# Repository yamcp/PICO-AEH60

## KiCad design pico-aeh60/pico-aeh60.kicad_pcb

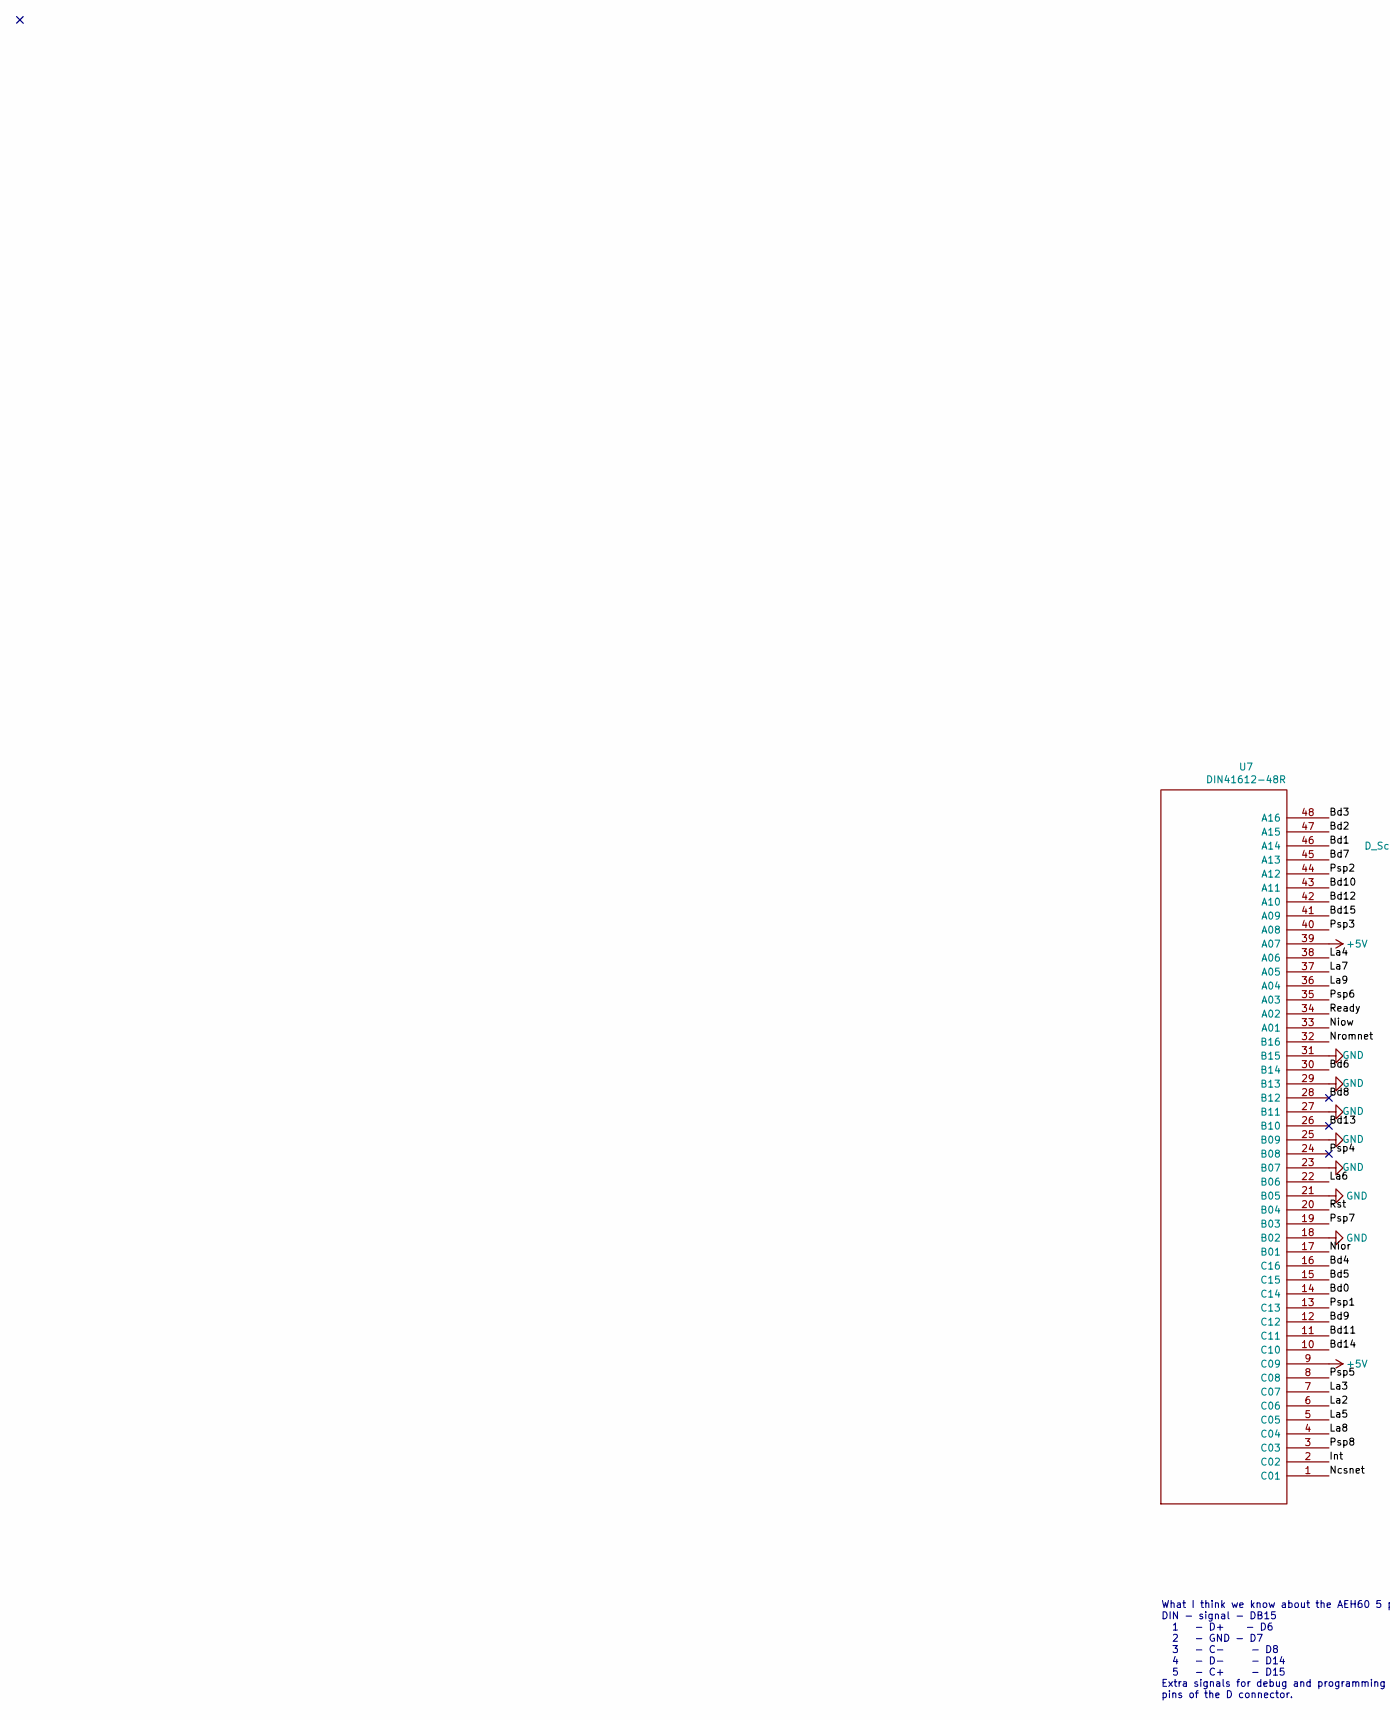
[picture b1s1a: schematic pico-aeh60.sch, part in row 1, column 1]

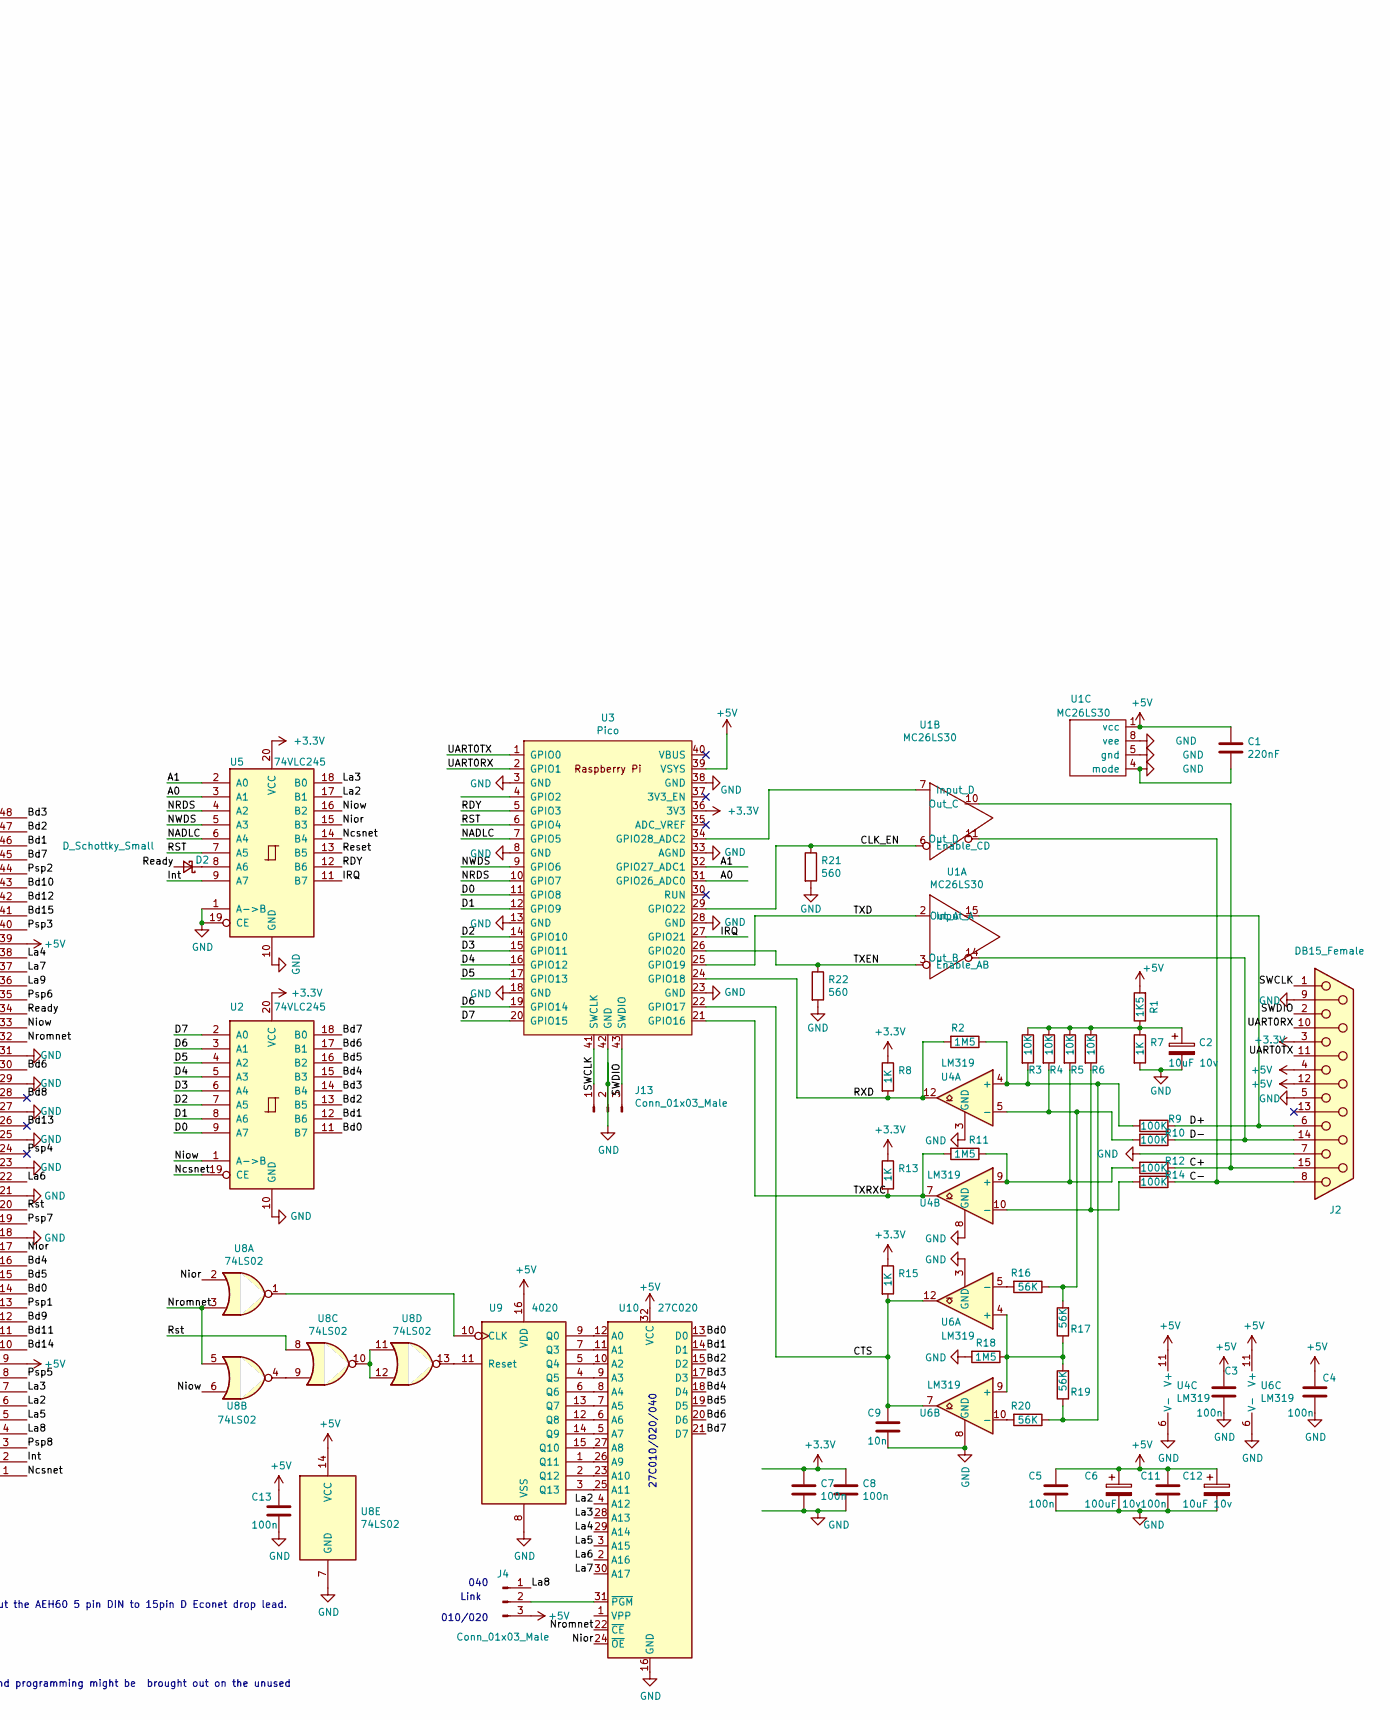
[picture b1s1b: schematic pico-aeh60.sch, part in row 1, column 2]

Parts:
C1: 220nF; C_0603_1608Metric_Pad1.08x0.95mm_HandSolder
C2: 10uF 10v; C_0805_2012Metric_Pad1.18x1.45mm_HandSolder
C3, C4, C5, C7, C8, C11, C13: 100n; C_0603_1608Metric_Pad1.08x0.95mm_HandSolder
C6: 100uF 10v; CP_Elec_8x6.2
C9: 10n; C_0603_1608Metric_Pad1.08x0.95mm_HandSolder
C12: 10uF 10v; CP_Elec_8x6.2
D2: D_Schottky_Small; D_SMA
J2: DB15_Female; DSUB-15_Female_Horizontal_P2.77x2.84mm_EdgePinOffset9.40mm
J4, J13: Conn_01x03_Male; PinHeader_1x03_P2.54mm_Vertical
R1: 1K5; R_0603_1608Metric_Pad0.98x0.95mm_HandSolder
R2, R11, R18: 1M5; R_0603_1608Metric_Pad0.98x0.95mm_HandSolder
R3, R4, R5, R6: 10K; R_0603_1608Metric_Pad0.98x0.95mm_HandSolder
R7, R8, R13, R15: 1K; R_0603_1608Metric_Pad0.98x0.95mm_HandSolder
R9, R10, R12, R14: 100K; R_0603_1608Metric_Pad0.98x0.95mm_HandSolder
R16, R17, R19, R20: 56K; R_0603_1608Metric_Pad0.98x0.95mm_HandSolder
R21, R22: 560; R_0603_1608Metric_Pad0.98x0.95mm_HandSolder
U1: MC26LS30; DIP-16_W7.62mm
U2, U5: 74VLC245; SOP-20_7.5x12.8mm_P1.27mm
U3: Pico; RPi_Pico_SMD_TH
U4, U6: LM319; SO-14_3.9x8.65mm_P1.27mm
U7: DIN41612-48R
U8: 74LS02; SO-14_3.9x8.65mm_P1.27mm
U9: 4020; SO-16_3.9x9.9mm_P1.27mm
U10: 27C020; DIP-32_W15.24mm_Socket

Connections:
+3V3: C7.1, C8.1, J2.3, R8.1, R13.1, R15.1, U2.20 (VCC), U3.36 (3V3), U5.20 (VCC)
+5V: C1.1, C3.1, C4.1, C5.1, C6.1, C11.1, C12.1, C13.1, J2.4, J2.12, J4.3, R1.2, U1.1 (vcc), U3.39 (VSYS), U4.11 (V+), U6.11 (V+), U7.9 (C09), U7.39 (A07), U8.14 (VCC), U9.16 (VDD), U10.32 (VCC)
/A0: U3.31 (GPIO26_ADC0), U5.3 (A1)
/A1: U3.32 (GPIO27_ADC1), U5.2 (A0)
/Bd0: U2.11 (B7), U7.14 (C14), U10.13 (D0)
/Bd1: U2.12 (B6), U7.46 (A14), U10.14 (D1)
/Bd2: U2.13 (B5), U7.47 (A15), U10.15 (D2)
/Bd3: U2.14 (B4), U7.48 (A16), U10.17 (D3)
/Bd4: U2.15 (B3), U7.16 (C16), U10.18 (D4)
/Bd5: U2.16 (B2), U7.15 (C15), U10.19 (D5)
/Bd6: U2.17 (B1), U7.30 (B14), U10.20 (D6)
/Bd7: U2.18 (B0), U7.45 (A13), U10.21 (D7)
/Bd8: U7.28 (B12)
/Bd9: U7.12 (C12)
/Bd10: U7.43 (A11)
/Bd11: U7.11 (C11)
/Bd12: U7.42 (A10)
/Bd13: U7.26 (B10)
/Bd14: U7.10 (C10)
/Bd15: U7.41 (A09)
/C+: J2.15, R12.1, U1.10 (Out_C)
/C-: J2.8, R14.1, U1.11 (Out_D)
/CLK_EN: R21.1, U1.6 (Enable_CD), U3.29 (GPIO22)
/CTS: C9.1, R15.2, U3.22 (GPIO17), U6.7, U6.12
/D0: U2.9 (A7), U3.11 (GPIO8)
/D1: U2.8 (A6), U3.12 (GPIO9)
/D2: U2.7 (A5), U3.14 (GPIO10)
/D3: U2.6 (A4), U3.15 (GPIO11)
/D4: U2.5 (A3), U3.16 (GPIO12)
/D5: U2.4 (A2), U3.17 (GPIO13)
/D6: U2.3 (A1), U3.19 (GPIO14)
/D7: U2.2 (A0), U3.20 (GPIO15)
/D+: J2.6, R9.1, U1.15 (Out_A)
/D-: J2.14, R10.1, U1.14 (Out_B)
/IRQ: U3.27 (GPIO21), U5.11 (B7)
/Int: U5.9 (A7), U7.2 (C02)
/La2: U5.17 (B1), U7.6 (C06), U10.4 (A12)
/La3: U5.18 (B0), U7.7 (C07), U10.28 (A13)
/La4: U7.38 (A06), U10.29 (A14)
/La5: U7.5 (C05), U10.3 (A15)
/La6: U7.22 (B06), U10.2 (A16)
/La7: U7.37 (A05), U10.30 (A17)
/La8: J4.1, U7.4 (C04)
/La9: U7.36 (A04)
/NADLC: U3.7 (GPIO5), U5.6 (A4)
/NRDS: U3.10 (GPIO7), U5.4 (A2)
/NWDS: U3.9 (GPIO6), U5.5 (A3)
/Ncsnet: U2.19 (CE), U5.14 (B4), U7.1 (C01)
/Nior: U5.15 (B3), U7.17 (B01), U8.2, U10.24 (~OE)
/Niow: U2.1 (A->B), U5.16 (B2), U7.33 (A01), U8.6
/Nromnet: U7.32 (B16), U8.3, U8.5, U10.22 (~CE)
/Psp1: U7.13 (C13)
/Psp2: U7.44 (A12)
/Psp3: U7.40 (A08)
/Psp4: U7.24 (B08)
/Psp5: U7.8 (C08)
/Psp6: U7.35 (A03)
/Psp7: U7.19 (B03)
/Psp8: U7.3 (C03)
/RDY: U3.5 (GPIO3), U5.12 (B6)
/RST: U3.6 (GPIO4), U5.7 (A5)
/RXD: R2.2, R8.2, U3.24 (GPIO18), U4.12
/Ready: D2.2 (A), U7.34 (A02)
/Reset: U5.13 (B5)
/Rst: U7.20 (B04), U8.8
/SWCLK: J2.1, J13.1, U3.41 (SWCLK)
/SWDIO: J2.2, J13.3, U3.43 (SWDIO)
/TXD: U1.2 (Input_A), U3.25 (GPIO19)
/TXEN: R22.1, U1.3 (Enable_AB), U3.26 (GPIO20)
/TXRXC: R11.2, R13.2, U3.21 (GPIO16), U4.7
/UART0RX: J2.10, U3.2 (GPIO1)
/UART0TX: J2.11 (P111), U3.1 (GPIO0)
GND: C1.2, C2.2, C3.2, C4.2, C5.2, C6.2, C7.2, C8.2, C9.2, C11.2, C12.2, C13.2, J2.5, J2.7, J2.9, J13.2, R7.2, R18.2, R21.2, R22.2, U1.4 (mode), U1.5 (gnd), U1.8 (vee), U2.10 (GND), U3.3 (GND), U3.8 (GND), U3.13 (GND), U3.18 (GND), U3.23 (GND), U3.28 (GND), U3.33 (AGND), U3.38 (GND), U3.42 (GND), U4.3 (GND), U4.6 (V-), U4.8 (GND), U5.1 (A->B), U5.10 (GND), U5.19 (CE), U6.3 (GND), U6.6 (V-), U6.8 (GND), U7.18 (B02), U7.21 (B05), U7.23 (B07), U7.25 (B09), U7.27 (B11), U7.29 (B13), U7.31 (B15), U8.7 (GND), U9.8 (VSS), U10.16 (GND)
unnamed: C2.1, R1.1, R3.1, R4.1, R5.1, R6.1, R7.1
unnamed: D2.1 (K), U5.8 (A6)
unnamed: J4.2, U10.31 (~PGM)
unnamed: R4.2, R10.2, R16.1, R17.2, U4.5 (-)
unnamed: R5.2, R11.1, R12.2, U4.9 (+)
unnamed: R6.2, R14.2, U4.10 (-)
unnamed: R16.2, U6.5 (-)
unnamed: R17.1, R18.1, R19.2, U6.4 (+), U6.9 (+)
unnamed: R2.1, R3.2, R9.2, R19.1, R20.1, U4.4 (+)
unnamed: R20.2, U6.10 (-)
unnamed: U1.7 (Input_D), U3.34 (GPIO28_ADC2)
unnamed: U8.1, U9.10 (CLK)
unnamed: U8.4, U8.9
unnamed: U8.10, U8.11, U8.12
unnamed: U8.13, U9.11 (Reset)
unnamed: U9.14 (Q9), U10.5 (A7)
unnamed: U9.12 (Q8), U10.6 (A6)
unnamed: U9.13 (Q7), U10.7 (A5)
unnamed: U9.6 (Q6), U10.8 (A4)
unnamed: U9.4 (Q5), U10.9 (A3)
unnamed: U9.5 (Q4), U10.10 (A2)
unnamed: U9.7 (Q3), U10.11 (A1)
unnamed: U9.9 (Q0), U10.12 (A0)
unnamed: U9.2 (Q12), U10.23 (A10)
unnamed: U9.3 (Q13), U10.25 (A11)
unnamed: U9.1 (Q11), U10.26 (A9)
unnamed: U9.15 (Q10), U10.27 (A8)

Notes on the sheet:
What I think we know about the AEH60 5 pin DIN to 15pin D Econet drop lead. DIN - signal - DB15 1 - D+ - D6 2 - GND - D7 3 - C- - D8 4 - D- - D14 5 - C+ - D15 Extra signals for debug and programming might be brought out on the unused pins of the D connector.
27C010/020/040
040
010/020
Link

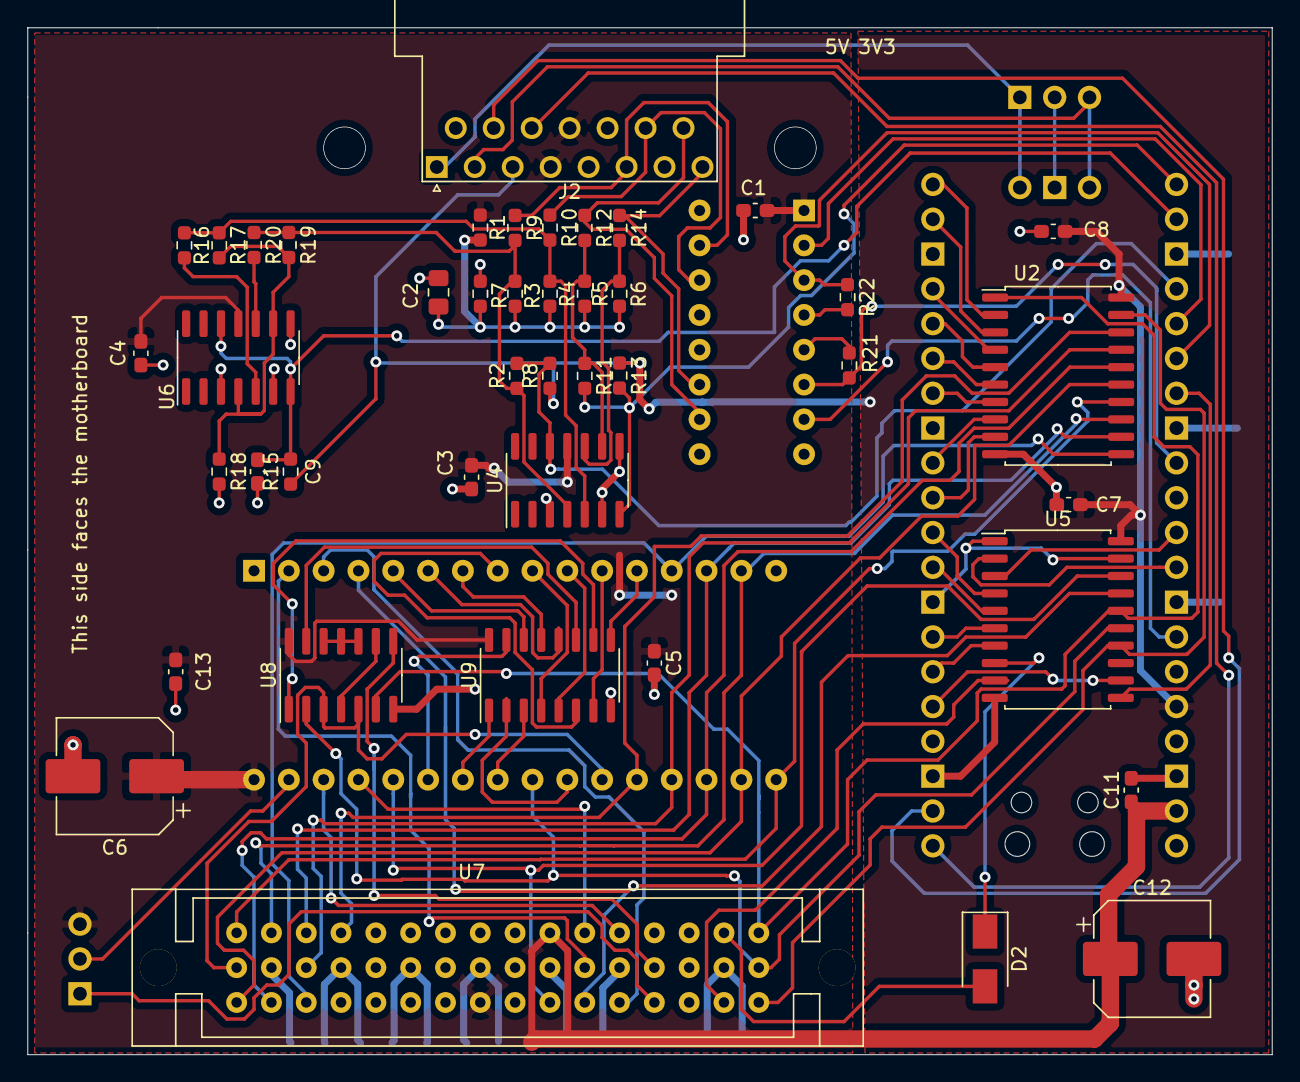
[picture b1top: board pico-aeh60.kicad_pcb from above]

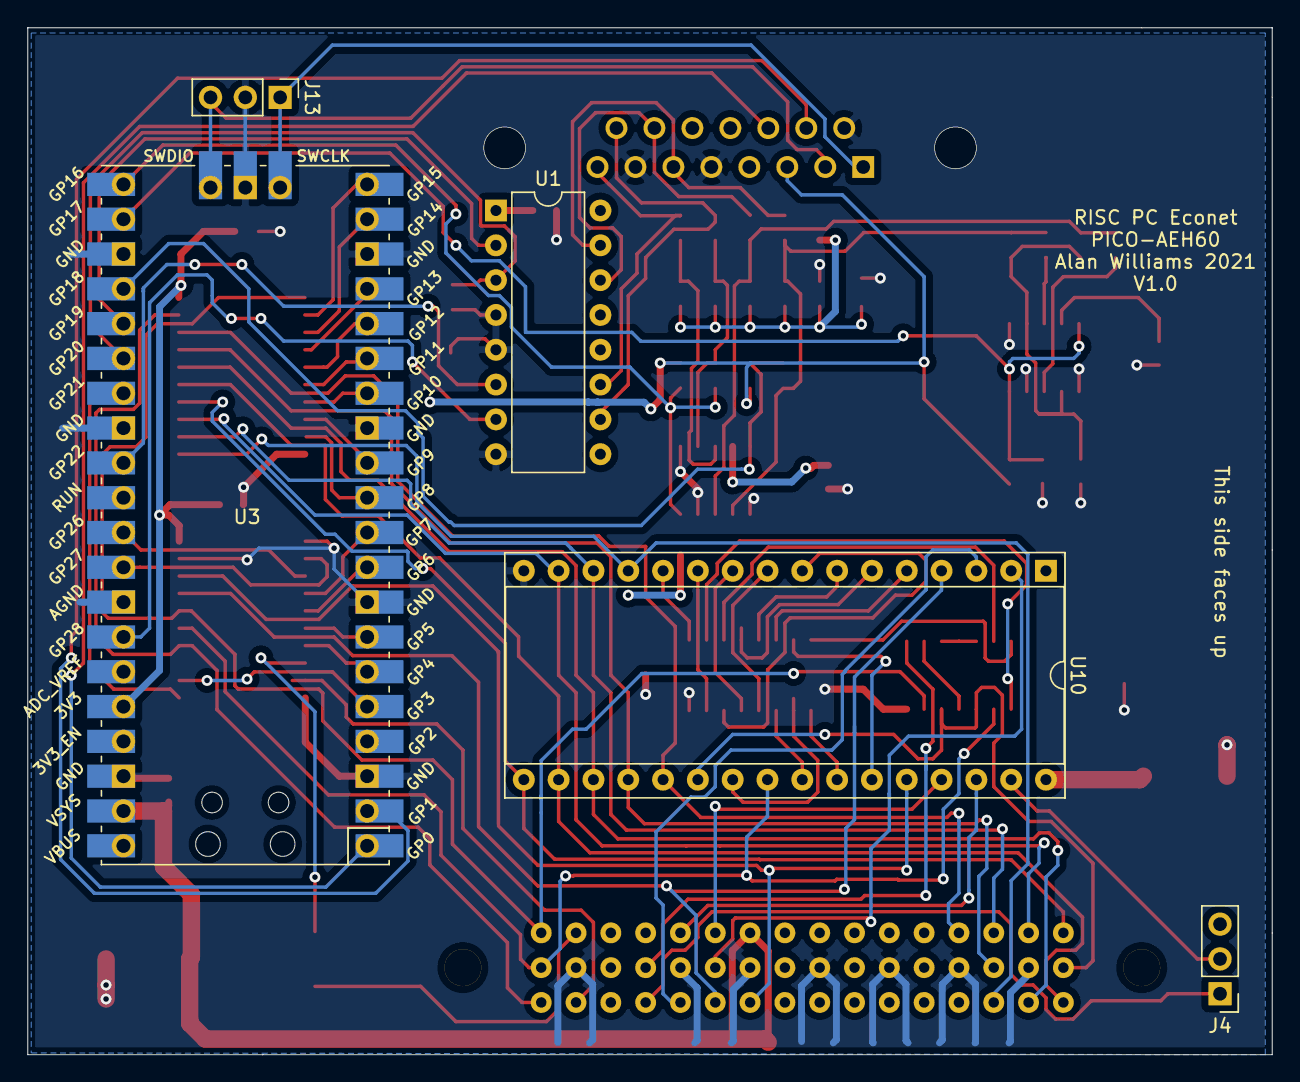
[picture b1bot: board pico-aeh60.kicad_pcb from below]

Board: 2 copper layers, 90.8 x 74.9 mm, 48 parts (5 on the bottom side), 82 nets.
